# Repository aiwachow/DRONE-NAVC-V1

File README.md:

# NAVIGATION CONTROL SYSTEM - TEST BOARD 
STM32 based flight controller for unmanned drone aircraft. <br />
Created mainly for testing and learning to write firmware. 

I am simultaneously designing a newer version of this controller: branch NAVC_V2. 

## Board

## Used software: 

## Visualization 
I also made basic 3D attitude visualization in Python. 

### Some theory behind attitude estimation in Polish 
[Attitude_Estimation_Theory_Adam_Iwachów.pdf](https://github.com/aiwachow/DRONE-NAVC-V1/files/14794682/Attitude_Estimation_Theory_Adam_Iwachow.pdf)

## Issues 
Pcb has been manufactured and tested. However this design isn't perfect. the main issues are: <br />
- PCB is quite too large, 
- selected microcontroller is difficult to access and was finally changed to STM32L4 .

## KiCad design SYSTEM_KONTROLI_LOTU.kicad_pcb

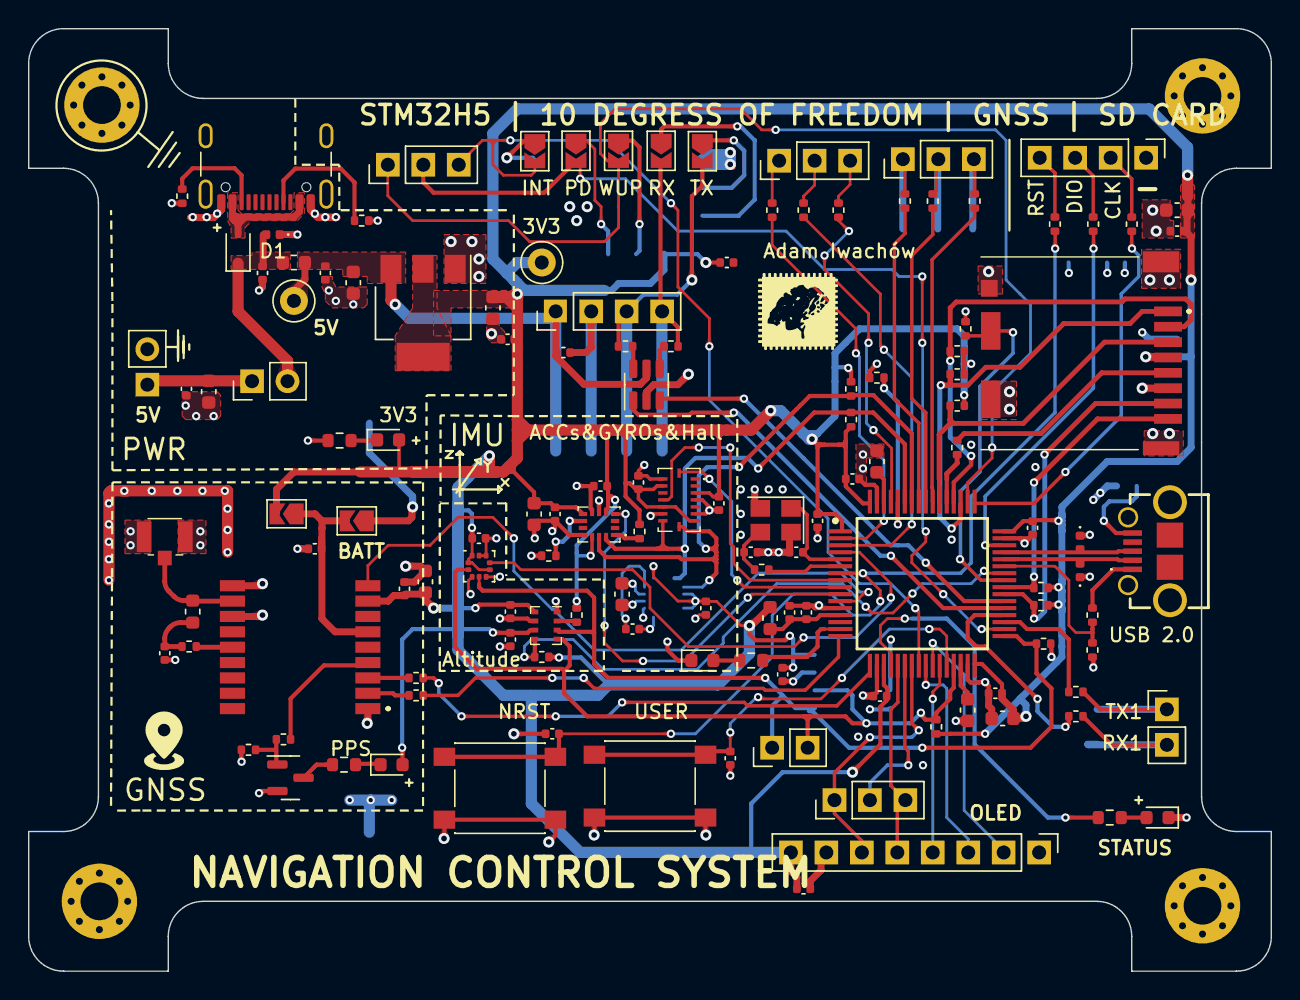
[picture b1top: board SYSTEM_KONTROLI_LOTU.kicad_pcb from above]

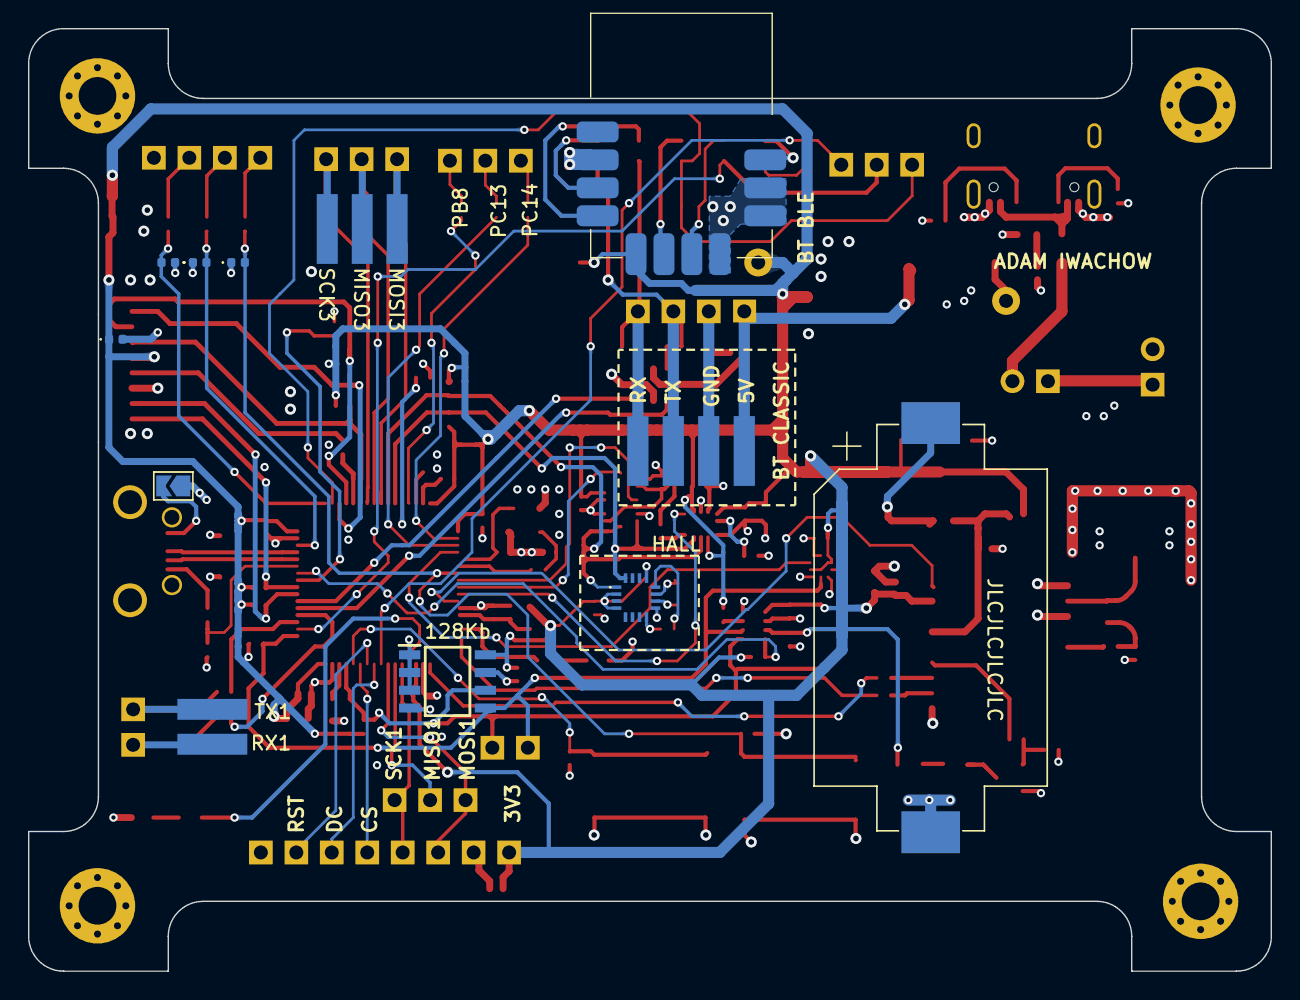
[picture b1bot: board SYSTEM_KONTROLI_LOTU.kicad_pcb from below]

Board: 4 copper layers, 89.0 x 67.5 mm, 145 parts (9 on the bottom side), 104 nets.

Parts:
BT1: CR2032; BatteryHolder_Keystone_1060_1x2032
C1, C2, C3, C5, C6, C101, C102, C103, C104, C105, C109, C130, C140, C302, C304, C402, C403, C408, C410, C411, C413, C415, C416, C417, C501, C502: 100n; C_0402_1005Metric
C4, C106, C412, C504: 4u7; C_0603_1608Metric
C107, C108, C301, C409: 2u2; C_0603_1608Metric
C110, C406: 1u; C_0402_1005Metric
C111, C120: 12pF; C_0402_1005Metric
C401: 10u; C_0603_1608Metric
C407: 10n; C_0402_1005Metric
C418: 220n; C_0402_1005Metric
C503: 1u; C_0603_1608Metric
D1: 5.5V|6V|15V; D_0402_1005Metric
D2, D4, D9, D10, D11, D201: 5.5V|6V|14V; D_0402_1005Metric
D3: LED_EMERALD; D_0603_1608Metric
D7: LED_BLUE; D_0603_1608Metric
D8: D_Schottky; D_SOD-323
D102: LED_WHITE; D_0603_1608Metric
D103: LED_RED; D_0603_1608Metric
FB2: 450m|600@100; L_0603_1608Metric
FB3: 100m|120@100MHz; L_0603_1608Metric
H1, H2, H3: MountingHole; MountingHole_2.7mm_Pad_Via
H4: MountingHole_Pad; MountingHole_2.7mm_Pad_Via
HM-BT4052: HM-BT4052
IC1: M24128-BFMN6TP; SOIC127P600X175-8N
IC2: STM32H562RGT6; QFP50P1200X1200X160-64N_newft
IC3: QMC5883L
IC6: ICM-42688-P; IIM42352
IC8: SIM68M|ATGM336H; ATGM336H5N31
IC9: BMI088
J1, J4, J6, J13: Conn_01x03; PinHeader_1x03_P2.54mm_Vertical
J3: Conn_01x08; PinHeader_1x08_P2.54mm_Vertical
J5: EXTERNAL USART; PinHeader_1x04_P2.54mm_Vertical
J7: Conn_I2C3; PinHeader_1x02_P2.54mm_Vertical
J8: Conn_01x04; PinHeader_1x04_P2.54mm_Vertical
J9: Conn_01x02; PinHeader_1x02_P2.54mm_Vertical
J10: DM3CS-SF; DM3CSSF
J11: USB_B_Micro; ZX62DB5PA830
J12: U.FL-R-SMT-1_80_; UFLRSMT180
J14: USB_C_Receptacle_USB2.0; USB_C_Receptacle_GCT_USB4105-xx-A_16P_TopMnt_Horizontal
J16: 5Vin; PinHeader_1x02_P2.54mm_Vertical
JP1, JP2, JP3, JP5, JP6, JP7, JP8, JP9: SolderJumper_2_Open; SolderJumper-2_P1.3mm_Open_TrianglePad1.0x1.5mm
JP4: Jumper_2_Open; PinHeader_1x02_P2.54mm_Vertical
L2: 27n|47n; L_0603_1608Metric
Q2: NPN; SOT-23
R1: 100k; R_0402_1005Metric
R2, R3, R105, R211, R302, R303, R304, R305, R306, R408, R409: 10k; R_0402_1005Metric
R101, R207, R208, R209, R307, R401, R402: 47; R_0402_1005Metric
R103, R104: 2k2; R_0603_1608Metric
R201, R202, R203, R204: 4k7; R_0402_1005Metric
R205, R206, R215, R216, R217, R218, R219: 470; R_0402_1005Metric
R210, R502, R503: 5k1; R_0402_1005Metric
R212, R213, R214, R403: 10; R_0402_1005Metric
R301: 1M; R_0402_1005Metric
R406: 2k2; R_0402_1005Metric
R407, R501: 1k; R_0603_1608Metric
SW1: NRST; SW_Push_1P1T_NO_6x6mm_H9.5mm
SW4: USER_BUTT; SW_Push_1P1T_NO_6x6mm_H9.5mm
TP1, TP2: TestPoint; TestPoint_Loop_D1.80mm_Drill1.0mm_Beaded
U1: LPS22HB; ST_HLGA-10_2x2mm_P0.5mm_LayoutBorder3x2y
U2: SPL06; Bosch_LGA-8_2x2.5mm_P0.65mm_ClockwisePinNumbering
U7: USBLC6-2SC6; SOT-23-6
U10: LDL1117S33R; SOT-223-3_TabPin2
Y1: HSE_25MHz|12pF; Crystal_SMD_3225-4Pin_3.2x2.5mm

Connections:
+3.3V: C1.1, C3.1, C6.1, C101.1, C102.1, C103.1, C104.1, C105.1, C106.1, C301.1, C302.1, C304.1, C401.1, C402.1, C407.1, C408.1, C409.1, C410.1, C411.1, C413.1, C415.1, C416.1, C417.1, C504.1, D3.2 (A), D7.2 (A), D9.1 (A1), FB2.1, HM-BT4052.7 (VDD), IC1.8 (VCC), IC2.1 (VBAT), IC2.19 (VDD_1), IC2.32 (VDD_2), IC2.48 (VDD_3), IC2.64 (VDD_4), IC3.2 (VDD), IC3.4 (S1), IC3.13 (VDDIO), IC6.5 (VDDIO), IC6.8 (VDD), IC6.12 (VDDIO), IC8.8 (VCC), IC9.3 (VDD), IC9.7 (PS), IC9.11 (VDDIO), IC9.14 (CSB1), J3.8, J10.4 (VDD), JP3.2 (B), R2.2, R3.2, R201.2, R202.2, R203.2, R204.2, R302.2, R303.2, R304.2, R305.2, R306.2, R409.1, TP2.1, U1.1 (Vdd_IO), U1.6 (~CS), U1.10 (VDD), U2.6 (Vdd_IO), U2.8 (VDD), U10.2 (VO)
+3.3VA: C109.1, C110.1, FB2.2, IC2.13 (VDDA)
+5V: C5.2, C502.1, C503.1, FB3.2, J5.1, TP1.1, U7.5 (VBUS), U10.3 (VI)
/NAVC_STM32 /NAVC_CONNECTORS/bT_INT: HM-BT4052.1 (INT), JP6.1 (A)
/NAVC_STM32 /NAVC_CONNECTORS/bT_PDN: HM-BT4052.5 (PDN), JP5.1 (A)
/NAVC_STM32 /NAVC_CONNECTORS/bT_WP: HM-BT4052.6 (WAKEUP), JP2.1 (A)
/NAVC_STM32 /NAVC_CONNECTORS/nAVC_MCS_INT2_PB8: J6.3, R217.1
/NAVC_STM32 /NAVC_CONNECTORS/nAVC_MCS_INT2_PC13: J6.1, R215.1
/NAVC_STM32 /NAVC_CONNECTORS/nAVC_MCS_INT2_PC14: J6.2, R216.1
/NAVC_STM32 /NAVC_CONNECTORS/nRST: J8.4, R207.1
/NAVC_STM32 /NAVC_CONNECTORS/sPI3_MISO: J13.2, R213.1
/NAVC_STM32 /NAVC_CONNECTORS/sPI3_MOSI: J13.1, R214.1
/NAVC_STM32 /NAVC_CONNECTORS/sPI3_SCK: J13.3, R212.1
/NAVC_STM32 /NAVC_CONNECTORS/sWCLK: J8.2, R208.2
/NAVC_STM32 /NAVC_CONNECTORS/sWDIO: J8.3, R209.2
/NAVC_STM32 /NAVC_CONNECTORS/uSART1_RX: J9.2, R218.2
/NAVC_STM32 /NAVC_CONNECTORS/uSART1_TX: J9.1, R219.2
/NAVC_STM32 /NAVC_CONNECTORS/usART6_RX: HM-BT4052.8 (UART_RXD), JP8.1 (A)
/NAVC_STM32 /NAVC_CONNECTORS/usART6_TX: HM-BT4052.9 (UART_TXD), JP7.1 (A)
/NAVC_STM32 /NAVC_MEMORY/sDMMC1_CLK: J10.5 (CLK), R307.2
/NAVC_STM32 /NAVC_POWER/5Vin: C2.1, C4.1, J16.1, JP4.1 (A)
/NAVC_STM32 /NAVC_POWER/Vusb: D8.2 (A), J14.A4 (VBUS), J14.A9 (VBUS), J14.B4 (VBUS), J14.B9 (VBUS)
/NAVC_STM32 /NAVC_SENSORS/antenna: IC8.11 (RF_IN), J12.1 (SIG), L2.2
/NAVC_STM32 /NAVC_SENSORS/uSART2_RX_GNSS: IC8.3 (RXD), R402.2
/NAVC_STM32 /NAVC_SENSORS/uSART2_TX_GNSS: IC8.2 (TXD), R401.2
/NAVC_STM32 /hSE_OUT: C120.1, R101.1, Y1.3
BACKUP: C406.1, IC8.6 (V_BCKP), JP1.2 (B), JP3.1 (A)
BMI088_INT1_ACC: IC2.9 (PC1), IC9.16 (INT1)
BMI088_INT3_GYRO: IC2.8 (PC0), IC9.12 (INT3)
BOOT0: IC2.60 (BOOT0), R105.1
BT_INT_PC4: IC2.24 (PC4), J1.3, JP6.2 (B)
BT_PDN_PB13: IC2.34 (PB13), J1.2, JP5.2 (B)
BT_WAKEUP_PA15: IC2.50 (PA15), J1.1, JP2.2 (B)
CARD_DETECT: IC2.41 (PA8), J10.10 (CARD_D), R301.2
CC1: J14.A5 (CC1), R502.1
CC2: J14.B5 (CC2), R503.1
GND: BT1.2 (-), C1.2, C2.2, C3.2, C4.2, C5.1, C6.2, C101.2, C102.2, C103.2, C104.2, C105.2, C106.2, C107.2, C108.2, C109.2, C110.2, C111.2, C120.2, C130.1, C140.1, C301.2, C302.2, C304.2, C401.2, C402.2, C403.2, C406.2, C407.2, C408.2, C409.2, C410.2, C411.2, C412.2, C413.2, C415.2, C416.2, C417.2, C501.2, C502.2, C503.2, C504.2, D1.1 (A1), D2.1 (A1), D4.1 (A1), D9.2 (A2), D10.1 (A1), D11.1 (A1), D102.1 (K), D103.1 (K), D201.1 (A1), H4.1, HM-BT4052.2 (GND), HM-BT4052.3 (GND), HM-BT4052.4 (GND), HM-BT4052.10 (GND), IC1.1 (E0), IC1.2 (E1), IC1.3 (E2), IC1.4 (VSS), IC1.7 (~WC), IC2.12 (VSSA), IC2.18 (VSS_1), IC2.31 (VSS_2), IC2.47 (VSS_3), IC2.63 (VSS_4), IC3.9 (GND_1), IC3.11 (GND_2), IC6.6 (GND), IC6.7 (RESV_3), IC6.11 (RESV_5), IC8.1 (GND), IC8.10 (GND), IC8.12 (GND), IC9.4 (GNDA), IC9.6 (GNDIO), IC9.10 (SDO2), IC9.15 (SDO1), J3.7, J5.2, J8.1, J10.6 (VSS), J10.9 (GND), J10.11 (GND), J10.12 (GND), J10.13 (GND), J12.2 (GND_1), J12.3 (GND_2), J14.A1 (GND), J14.A12 (GND), J14.B1 (GND), J14.B12 (GND), J16.2, JP9.1 (A), Q2.2 (E), R1.1, R105.2, R211.1, R301.1, R408.1, R501.1, R502.2, R503.2, SW1.3 (B), SW4.3 (B), U1.3 (RES), U1.5 (SA0), U1.8 (GND), U1.9 (GND), U2.1 (GND), U2.7 (GND), U7.2 (GND), U10.1 (GND), Y1.2, Y1.4
GNSS_NRST: IC2.11 (PC3), IC8.9 (RESET_N)
HSE_IN: C111.1, IC2.5 (PH0-OSC_IN), Y1.1
HSE_OUT: IC2.6 (PH1-OSC_OUT), R101.2
I2C1_SCK: IC2.58 (PB6), IC3.1 (SCL), IC6.13 (SCK), IC9.8 (SCL/SCK), R202.1
I2C1_SDA: IC2.59 (PB7), IC3.16 (SDA), IC6.14 (SDA), IC9.9 (SDA/SDI), R201.1
I2C2_SCK: IC1.6 (SCL), IC2.29 (PB10), J7.2, R204.1, U1.2 (SCL), U2.4 (SCL)
I2C2_SDA: IC1.5 (SDA), IC2.33 (PB12), J7.1, R203.1, U1.4 (SDA), U2.3 (SDA)
ICM_INT1: IC2.10 (PC2), IC6.4 (INT1_/_INT)
LED2: IC2.15 (PA1), R103.2
LED3: IC2.20 (PA4), R104.2
LPS22_DRDY: IC2.4 (PC15-OSC32_OUT), U1.7 (INT_DRDY)
NAVC_MCS_INT1_PC14: IC2.3 (PC14-OSC32_IN), R216.2
NAVC_MCS_INT2_PC13: IC2.2 (PC13), R215.2
NAVC_MCS_INT3_PB8: IC2.61 (PB8), R217.2
NRST: C130.2, D201.2 (A2), IC2.7 (NRST), R207.2, SW1.1 (A)
unnamed: BT1.1 (+), JP1.1 (A)
unnamed: C403.1, L2.1, R403.2
unnamed: D3.1 (K), R501.2
unnamed: D7.1 (K), R407.2
unnamed: D102.2 (A), R103.1
unnamed: D103.2 (A), R104.1
unnamed: C412.1, IC3.10 (C1)
unnamed: C418.2, IC3.12 (SETC)
unnamed: C418.1, IC3.8 (STEP)
unnamed: IC6.1 (AP_SDO), R409.2
unnamed: IC6.9 (INT2), R408.2
unnamed: IC8.14 (VCC_RF), R403.1
unnamed: J11.5 (GND), JP9.2 (B)
unnamed: J11.1 (VBUS), R210.1
unnamed: Q2.1 (B), R1.2, R406.2
unnamed: Q2.3 (C), R407.1
unnamed: R205.1, U7.4 (I/O2)
unnamed: R206.1, U7.6 (I/O1)
unnamed: R3.1, U2.2 (~CS)
OLED_CS: IC2.27 (PB1), J3.4
OLED_DC: IC2.25 (PC5), J3.3
OLED_RST: IC2.26 (PB0), J3.2
SDMMC1_CLK: IC2.53 (PC12), R307.1
SDMMC1_CMD: IC2.54 (PD2), J10.3 (CMD), R302.1
SDMMC1_D0: IC2.39 (PC8), J10.7 (DAT0), R303.1
SDMMC1_D1: IC2.40 (PC9), J10.8 (DAT1), R304.1
SDMMC1_D2: IC2.51 (PC10), J10.1 (DAT2), R305.1
SDMMC1_D3: IC2.52 (PC11), J10.2 (CD/DAT3), R306.1
SLP_INT: IC2.42 (PA9), R2.1, U2.5 (SD0)
SPI1_MISO: IC2.22 (PA6), J4.2
SPI1_MOSI: IC2.23 (PA7), J3.6, J4.1
SPI1_SCK: IC2.21 (PA5), J3.5, J4.3
SPI3_MISO: IC2.56 (PB4), R213.2
SPI3_MOSI: IC2.57 (PB5), R214.2
SPI3_SCK: IC2.55 (PB3), R212.2
SWCLK: D4.2 (A2), IC2.49 (PA14), R208.1
SWDIO: D2.2 (A2), IC2.46 (PA13), R209.1
TIMEMARK: IC8.4 (1PPS), R406.1
USART1_RX: IC2.36 (PB15), R218.1
USART1_TX: IC2.35 (PB14), R219.1
USART2_RX_GNSS: IC2.17 (PA3), R402.1
USART2_TX_GNSS: IC2.16 (PA2), R401.1
USART6_RX: IC2.38 (PC7), U7.3 (I/O2)
USART6_TX: IC2.37 (PC6), U7.1 (I/O1)
USB_DN: D11.2 (A2), IC2.44 (PA11), J11.2 (D-)
USB_DP: D10.2 (A2), IC2.45 (PA12), J11.3 (D+)
USB_OTG_STAT: IC2.43 (PA10), R210.2, R211.2
USER_BUTT: C140.2, IC2.28 (PB2), SW4.1 (A)
VBUS: C501.1, D1.2 (A2), D8.1 (K), FB3.1, JP4.2 (B)
Vcap: C107.1, C108.1, IC2.30 (VCAP_1), IC2.62 (VCAP_2)
uSART6_RX: J5.4, JP8.2 (B), R205.2
uSART6_TX: J5.3, JP7.2 (B), R206.2

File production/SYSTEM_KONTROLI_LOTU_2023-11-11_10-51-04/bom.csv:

Designator,Footprint,Quantity,Value,LCSC Part #
BT1,BatteryHolder_Keystone_1060_1x2032,1,CR2032,
C1, C101, C102, C103, C104, C105, C109, C130, C140, C2, C3, C302, C304, C402, C403, C408, C410, C411, C413, C415, C416, C417, C5, C501, C502, C6,0402,26,100n,C307331
C106, C4, C412, C504,0603,4,4u7,C19666
C107, C108, C301, C409,0603,4,2u2,C23630
C110, C406,0402,2,1u,C52923
C111, C120,0402,2,12pF,C1547
C401,0603,1,10u,C96446
C407,0402,1,10n,C15195
C418,0402,1,220n,C16772
C503,0603,1,1u,C15849
D1,0402,1,5.5V|6V|15V,
D10, D11, D2, D201, D4, D9,0402,6,5.5V|6V|14V,
D102,0603,1,LED_WHITE,C2290
D103,0603,1,LED_RED,C2286
D3,0603,1,LED_EMERALD,C72043
D7,0603,1,LED_BLUE,C72041
D8,D_SOD-323,1,D_Schottky,C191023
FB2,0603,1,450m|600@100,C1002
FB3,0603,1,100m|120@100MHz,
H1, H2, H3,MountingHole_2.7mm_Pad_Via,3,MountingHole,
H4,MountingHole_2.7mm_Pad_Via,1,MountingHole_Pad,
HM-BT4052,HM-BT4052,1,~,
IC1,SOIC127P600X175-8N,1,M24128-BFMN6TP,
IC2,QFP50P1200X1200X160-64N_newft,1,STM32H562RGT6,
IC3,QMC5883L,1,QMC5883L,
IC6,IIM42352,1,ICM-42688-P,C1850418
IC8,ATGM336H5N31,1,SIM68M|ATGM336H,
IC9,BMI088,1,BMI088,C194919
J1, J13, J4, J6,PinHeader_1x03_P2.54mm_Vertical,4,Conn_01x03,
J10,DM3CSSF,1,DM3CS-SF,
J11,ZX62DB5PA830,1,USB_B_Micro,
J12,UFLRSMT180,1,U.FL-R-SMT-1_80_,
J14,USB_C_Receptacle_GCT_USB4105-xx-A_16P_TopMnt_Horizontal,1,USB_C_Receptacle_USB2.0,
J16,PinHeader_1x02_P2.54mm_Vertical,1,5Vin,
J3,PinHeader_1x08_P2.54mm_Vertical,1,Conn_01x08,
J5,PinHeader_1x04_P2.54mm_Vertical,1,EXTERNAL USART,
J7,PinHeader_1x02_P2.54mm_Vertical,1,Conn_I2C3,
J8,PinHeader_1x04_P2.54mm_Vertical,1,Conn_01x04,
J9,PinHeader_1x02_P2.54mm_Vertical,1,Conn_01x02,
JP1, JP2, JP3, JP5, JP6, JP7, JP8, JP9,SolderJumper-2_P1.3mm_Open_TrianglePad1.0x1.5mm,8,SolderJumper_2_Open,
JP4,PinHeader_1x02_P2.54mm_Vertical,1,Jumper_2_Open,
L2,0603,1,27n|47n,
Q2,SOT-23,1,NPN,C20526
R1,0402,1,100k,C25741
R101, R207, R208, R209, R307, R401, R402,0402,7,47,C25092
R103, R104,0603,2,2k2,C4190
R105, R2, R211, R3, R302, R303, R304, R305, R306, R408, R409,0402,11,10k,C25744
R201, R202, R203, R204,0402,4,4k7,C25900
R205, R206, R215, R216, R217, R218, R219,0402,7,470,C25117
R210, R502, R503,0402,3,5k1,C25905
R212, R213, R214, R403,0402,4,10,C25077
R301,0402,1,1M,C26083
R406,0402,1,2k2,C4190
R407, R501,0603,2,1k,C21190
SW1,SW_Push_1P1T_NO_6x6mm_H9.5mm,1,NRST,
SW4,SW_Push_1P1T_NO_6x6mm_H9.5mm,1,USER_BUTT,
TP1, TP2,TestPoint_Loop_D1.80mm_Drill1.0mm_Beaded,2,TestPoint,
U1,ST_HLGA-10_2x2mm_P0.5mm_LayoutBorder3x2y,1,LPS22HB,C94049
U10,SOT-223-3_TabPin2,1,LDL1117S33R,
U2,Bosch_LGA-8_2x2.5mm_P0.65mm_ClockwisePinNumbering,1,SPL06,C2684428
U7,SOT-23-6,1,USBLC6-2SC6,
Y1,Crystal_SMD_3225-4Pin_3.2x2.5mm,1,HSE_25MHz|12pF,C9006

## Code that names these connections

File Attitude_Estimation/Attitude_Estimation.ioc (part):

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Mcu.Name=STM32L476R(C-E-G)Tx
Mcu.Package=LQFP64
Mcu.UserName=STM32L476RGTx
PA10.Mode=Asynchronous
PA10.Signal=USART1_RX
PA13\ (JTMS-SWDIO).Mode=Serial_Wire
PA13\ (JTMS-SWDIO).Signal=SYS_JTMS-SWDIO
PA14\ (JTCK-SWCLK).Mode=Serial_Wire
PA14\ (JTCK-SWCLK).Signal=SYS_JTCK-SWCLK
PA2.Mode=Asynchronous
PA2.Signal=USART2_TX
PA3.Mode=Asynchronous
PA3.Signal=USART2_RX
PA9.Mode=Asynchronous
PA9.Signal=USART1_TX
PB10.GPIOParameters=GPIO_Label
PB10.GPIO_Label=Sensors_Led
PB10.Signal=GPIO_Output
PB11.GPIOParameters=GPIO_Label
PB11.GPIO_Label=Status_Led
PB11.Signal=GPIO_Output
PB13.Mode=I2C
PB13.Signal=I2C2_SCL
PB14.Mode=I2C
PB14.Signal=I2C2_SDA
PB8.Mode=I2C
PB8.Signal=I2C1_SCL
PB9.Mode=I2C
PB9.Signal=I2C1_SDA
PC1.GPIOParameters=GPIO_Label
PC1.GPIO_Label=SPL_INT
PC1.Signal=GPXTI1
PC11.GPIOParameters=GPIO_Label
PC11.GPIO_Label=LPS25_INT
PC11.Signal=GPXTI11
PC2.GPIOParameters=GPIO_Label
PC2.GPIO_Label=BMI_ACC_INT
PC2.Signal=GPXTI2
PC3.GPIOParameters=GPIO_Label
PC3.GPIO_Label=BMI_GYRO_INT
PC3.Signal=GPXTI3
PC9.GPIOParameters=GPIO_PuPd,GPIO_Label,GPIO_ModeDefaultEXTI
PC9.GPIO_Label=USER_BUTT
PC9.GPIO_ModeDefaultEXTI=GPIO_MODE_IT_FALLING
PC9.GPIO_PuPd=GPIO_PULLUP
PC9.Signal=GPXTI9
RCC.HSE_VALUE=8000000
RCC.SYSCLKFreq_VALUE=80000000
RCC.SYSCLKSource=RCC_SYSCLKSOURCE_PLLCLK
board=custom

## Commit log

2024-02-26 3D python visualization
2024-02-28 adding schematics
2024-02-28 rest of the files
2024-03-30 New branch creating
2024-03-30 Deleting some files
2024-04-02 visual changes
